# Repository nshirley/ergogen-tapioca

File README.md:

### Overview
This is built with [Ergogen](https://github.com/ergogen/ergogen), and is my attempt to using the Cherry MX ULP switches. Documentation and availability of these switches is _severely_ lacking, so I make no promises that this works, will always work, or is in any way the best way to do this.

If you see something that can be improved, please feel free to open a PR!

### What's Next?
To see what I have planned next, need to tackle, or just curious where this project is going, check out the [roadmap](ROADMAP.md), or open [Issues](https://github.com/nshirley/ergogen-tapioca/issues)!

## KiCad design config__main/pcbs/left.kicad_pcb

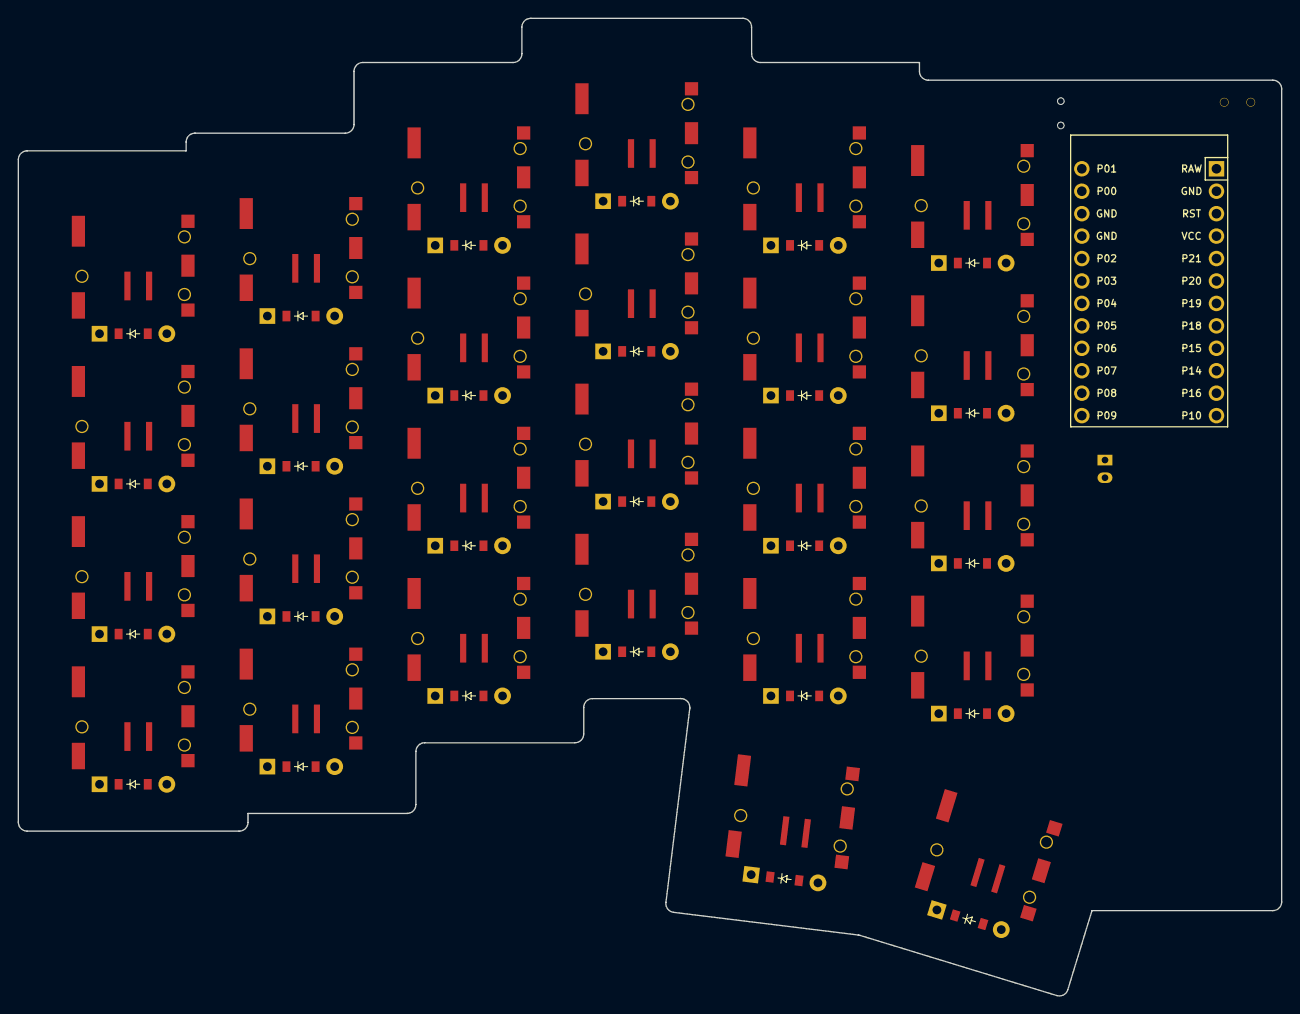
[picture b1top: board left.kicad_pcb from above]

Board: 2 copper layers, 143.0 x 110.7 mm, 56 parts (0 on the bottom side), 41 nets, no tracks yet.

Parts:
B1: Panasonic_EVQPUL_EVQPUC
D1, D2, D3, D4, D5, D6, D7, D8, D9, D10, D11, D12, D13, D14, D15, D16, D17, D18, D19, D20, D21, D22, D23, D24, D25, D26: ComboDiode
JST1: JST_PH_S2B-PH-K_02x2.00mm_Angled
MCU1: ProMicro
S1, S2, S3, S4, S5, S6, S7, S8, S9, S10, S11, S12, S13, S14, S15, S16, S17, S18, S19, S20, S21, S22, S23, S24, S25, S26: Cherry_ULP_SMD
T1: SPDT_C128955

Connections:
GND: B1.1, JST1.2, MCU1.2, MCU1.15, MCU1.16
P2: D25.1, D26.1, MCU1.17
P3: D1.1, D5.1, D9.1, D13.1, D17.1, D21.1, MCU1.18
P4: D2.1, D6.1, D10.1, D14.1, D18.1, D22.1, MCU1.19
P5: D3.1, D7.1, D11.1, D15.1, D19.1, D23.1, MCU1.20
P6: D4.1, D8.1, D12.1, D16.1, D20.1, D24.1, MCU1.21
P10: MCU1.12, S21.1, S22.1, S23.1, S24.1, S26.1
P14: MCU1.10, S13.1, S14.1, S15.1, S16.1
P15: MCU1.9, S9.1, S10.1, S11.1, S12.1
P16: MCU1.11, S17.1, S18.1, S19.1, S20.1, S25.1
P18: MCU1.8, S5.1, S6.1, S7.1, S8.1
P19: MCU1.7, S1.1, S2.1, S3.1, S4.1
RAW: MCU1.1, T1.2
RST: B1.2, MCU1.3
home_thumb: D26.2, S26.2
index_bottom: D18.2, S18.2
index_home: D19.2, S19.2
index_mod: D17.2, S17.2
index_top: D20.2, S20.2
inner_bottom: D22.2, S22.2
inner_home: D23.2, S23.2
inner_mod: D21.2, S21.2
inner_thumb: D25.2, S25.2
inner_top: D24.2, S24.2
middle_bottom: D14.2, S14.2
middle_home: D15.2, S15.2
middle_mod: D13.2, S13.2
middle_top: D16.2, S16.2
outer_bottom: D2.2, S2.2
outer_home: D3.2, S3.2
outer_mod: D1.2, S1.2
outer_top: D4.2, S4.2
pinky_bottom: D6.2, S6.2
pinky_home: D7.2, S7.2
pinky_mod: D5.2, S5.2
pinky_top: D8.2, S8.2
pos: JST1.1, T1.1
ring_bottom: D10.2, S10.2
ring_home: D11.2, S11.2
ring_mod: D9.2, S9.2
ring_top: D12.2, S12.2

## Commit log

2024-12-01 initial commit, ish
2024-12-01 remove output dir
2024-12-01 add readme and roadmap docs
2024-12-02 start changing over to polygon for outline
